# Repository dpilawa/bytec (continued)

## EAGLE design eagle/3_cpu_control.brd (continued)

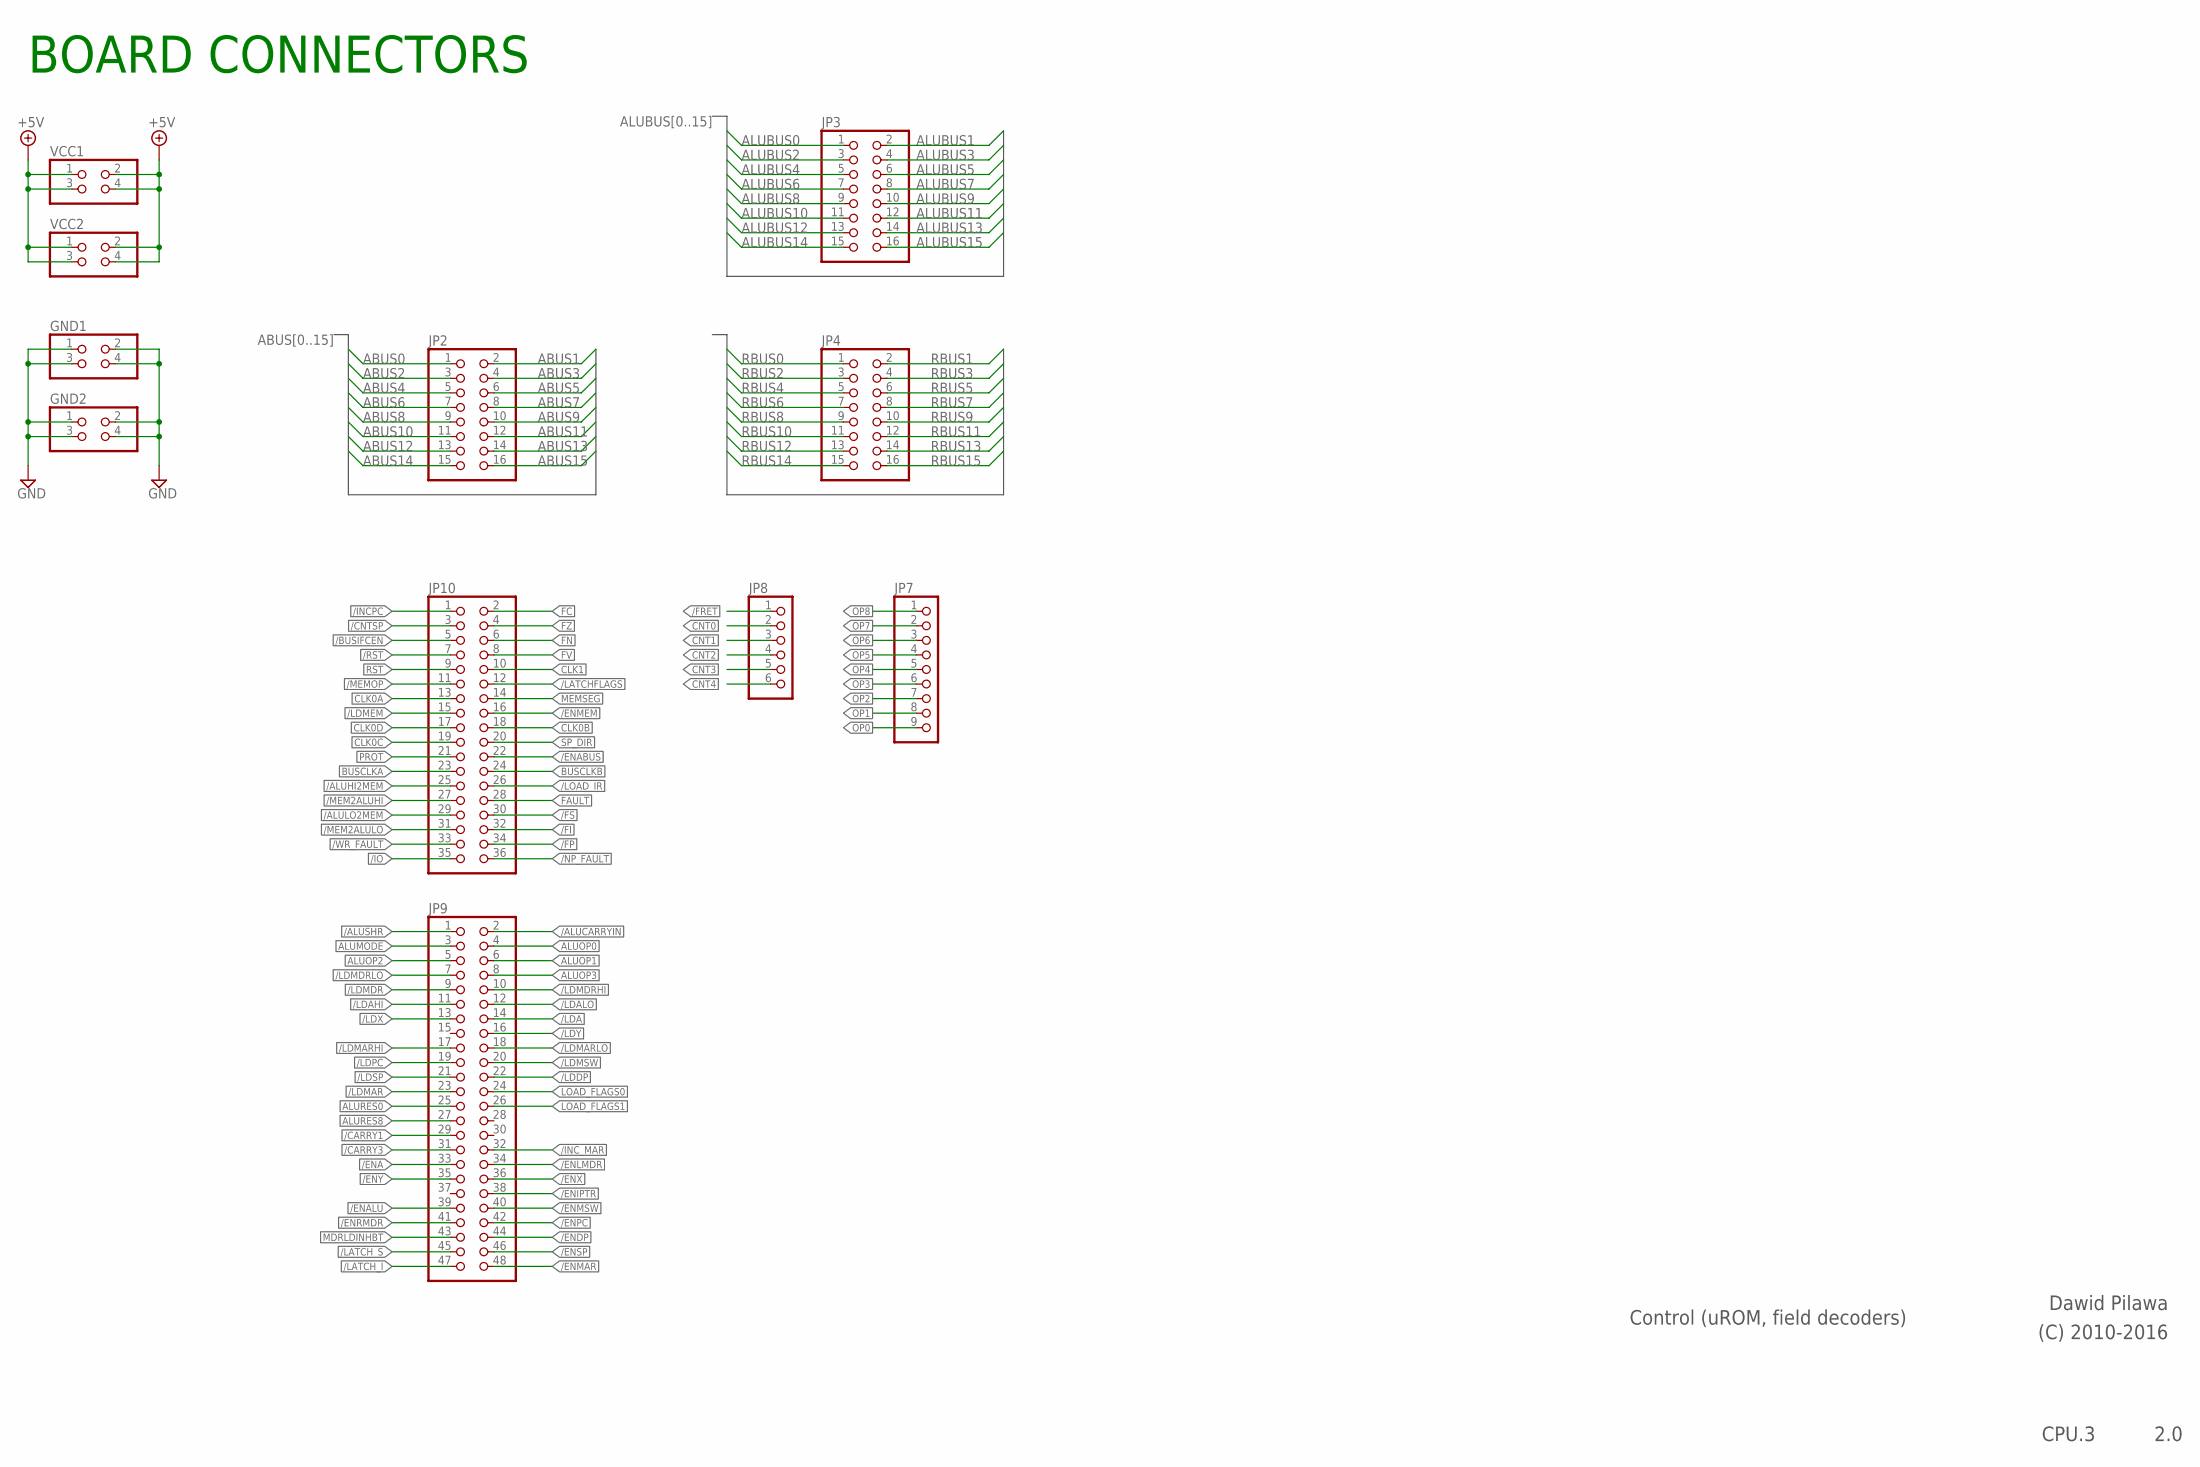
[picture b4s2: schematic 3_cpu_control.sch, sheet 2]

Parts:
GND1, GND2: PINHD-2X2; 2X02
JP2, JP3, JP4: PINHD-2X8; 2X08
JP7: PINHD-1X9; 1X09
JP8: PINHD-1X6; 1X06
JP9: PINHD-2X24; 2X24
JP10: PINHD-2X18; 2X18
VCC1, VCC2: PINHD-2X2; 2X02

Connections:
+5V: VCC1.1, VCC1.2, VCC1.3, VCC1.4, VCC2.1, VCC2.2, VCC2.3, VCC2.4; also elsewhere on the board
/ALUCARRYIN: JP9.2; also elsewhere on the board
/ALUHI2MEM: JP10.25; also elsewhere on the board
/ALULO2MEM: JP10.29; also elsewhere on the board
/ALUSHR: JP9.1; also elsewhere on the board
/BUSIFCEN: JP10.5; also elsewhere on the board
/CARRY1: JP9.29
/CARRY3: JP9.31
/CNTSP: JP10.3; also elsewhere on the board
/ENA: JP9.33; also elsewhere on the board
/ENABUS: JP10.22; also elsewhere on the board
/ENALU: JP9.39; also elsewhere on the board
/ENDP: JP9.44; also elsewhere on the board
/ENIPTR: JP9.38; also elsewhere on the board
/ENLMDR: JP9.34; also elsewhere on the board
/ENMAR: JP9.48; also elsewhere on the board
/ENMEM: JP10.16; also elsewhere on the board
/ENMSW: JP9.40; also elsewhere on the board
/ENPC: JP9.42; also elsewhere on the board
/ENRMDR: JP9.41; also elsewhere on the board
/ENSP: JP9.46; also elsewhere on the board
/ENX: JP9.36; also elsewhere on the board
/ENY: JP9.35; also elsewhere on the board
/FI: JP10.32
/FP: JP10.34
/FRET: JP8.1; also elsewhere on the board
/FS: JP10.30
/INCPC: JP10.1; also elsewhere on the board
/INC_MAR: JP9.32; also elsewhere on the board
/IO: JP10.35
/LATCHFLAGS: JP10.12; also elsewhere on the board
/LATCH_I: JP9.47; also elsewhere on the board
/LATCH_S: JP9.45; also elsewhere on the board
/LDA: JP9.14; also elsewhere on the board
/LDAHI: JP9.11; also elsewhere on the board
/LDALO: JP9.12; also elsewhere on the board
/LDDP: JP9.22; also elsewhere on the board
/LDMAR: JP9.23; also elsewhere on the board
/LDMARHI: JP9.17; also elsewhere on the board
/LDMARLO: JP9.18; also elsewhere on the board
/LDMDR: JP9.9; also elsewhere on the board
/LDMDRHI: JP9.10; also elsewhere on the board
/LDMDRLO: JP9.7; also elsewhere on the board
/LDMEM: JP10.15; also elsewhere on the board
/LDMSW: JP9.20; also elsewhere on the board
/LDPC: JP9.19; also elsewhere on the board
/LDSP: JP9.21; also elsewhere on the board
/LDX: JP9.13; also elsewhere on the board
/LDY: JP9.16; also elsewhere on the board
/LOAD_IR: JP10.26; also elsewhere on the board
/MEM2ALUHI: JP10.27; also elsewhere on the board
/MEM2ALULO: JP10.31; also elsewhere on the board
/MEMOP: JP10.11; also elsewhere on the board
/NP_FAULT: JP10.36
/RST: JP10.7
/WR_FAULT: JP10.33
ABUS0: JP2.1
ABUS1: JP2.2
ABUS2: JP2.3
ABUS3: JP2.4
ABUS4: JP2.5
ABUS5: JP2.6
ABUS6: JP2.7
ABUS7: JP2.8
ABUS8: JP2.9
ABUS9: JP2.10
ABUS10: JP2.11
ABUS11: JP2.12
ABUS12: JP2.13
ABUS13: JP2.14
ABUS14: JP2.15
ABUS15: JP2.16
ALUBUS0: JP3.1
ALUBUS1: JP3.2
ALUBUS2: JP3.3
ALUBUS3: JP3.4
ALUBUS4: JP3.5
ALUBUS5: JP3.6
ALUBUS6: JP3.7
ALUBUS7: JP3.8
ALUBUS8: JP3.9
ALUBUS9: JP3.10
ALUBUS10: JP3.11
ALUBUS11: JP3.12
ALUBUS12: JP3.13
ALUBUS13: JP3.14
ALUBUS14: JP3.15
ALUBUS15: JP3.16
ALUMODE: JP9.3; also elsewhere on the board
ALUOP0: JP9.4; also elsewhere on the board
ALUOP1: JP9.6; also elsewhere on the board
ALUOP2: JP9.5; also elsewhere on the board
ALUOP3: JP9.8; also elsewhere on the board
ALURES0: JP9.25
ALURES8: JP9.27
BUSCLKA: JP10.23; also elsewhere on the board
BUSCLKB: JP10.24
CLK0A: JP10.13
CLK0B: JP10.18
CLK0C: JP10.19
CLK0D: JP10.17; also elsewhere on the board
CLK1: JP10.10
CNT0: JP8.2; also elsewhere on the board
CNT1: JP8.3; also elsewhere on the board
CNT2: JP8.4; also elsewhere on the board
CNT3: JP8.5; also elsewhere on the board
CNT4: JP8.6; also elsewhere on the board
FAULT: JP10.28; also elsewhere on the board
FC: JP10.2; also elsewhere on the board
FN: JP10.6; also elsewhere on the board
FV: JP10.8; also elsewhere on the board
FZ: JP10.4; also elsewhere on the board
GND: GND1.1, GND1.2, GND1.3, GND1.4, GND2.1, GND2.2, GND2.3, GND2.4; also elsewhere on the board
LOAD_FLAGS0: JP9.24; also elsewhere on the board
LOAD_FLAGS1: JP9.26; also elsewhere on the board
MDRLDINHBT: JP9.43; also elsewhere on the board
MEMSEG: JP10.14; also elsewhere on the board
OP0: JP7.9; also elsewhere on the board
OP1: JP7.8; also elsewhere on the board
OP2: JP7.7; also elsewhere on the board
OP3: JP7.6; also elsewhere on the board
OP4: JP7.5; also elsewhere on the board
OP5: JP7.4; also elsewhere on the board
OP6: JP7.3; also elsewhere on the board
OP7: JP7.2; also elsewhere on the board
OP8: JP7.1; also elsewhere on the board
PROT: JP10.21; also elsewhere on the board
RBUS0: JP4.1
RBUS1: JP4.2
RBUS2: JP4.3
RBUS3: JP4.4
RBUS4: JP4.5
RBUS5: JP4.6
RBUS6: JP4.7
RBUS7: JP4.8
RBUS8: JP4.9
RBUS9: JP4.10
RBUS10: JP4.11
RBUS11: JP4.12
RBUS12: JP4.13
RBUS13: JP4.14
RBUS14: JP4.15
RBUS15: JP4.16
RST: JP10.9
SP_DIR: JP10.20; also elsewhere on the board

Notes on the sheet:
Control (uROM, field decoders)
2.0
Dawid Pilawa
(C) 2010-2016
CPU.3
BOARD CONNECTORS

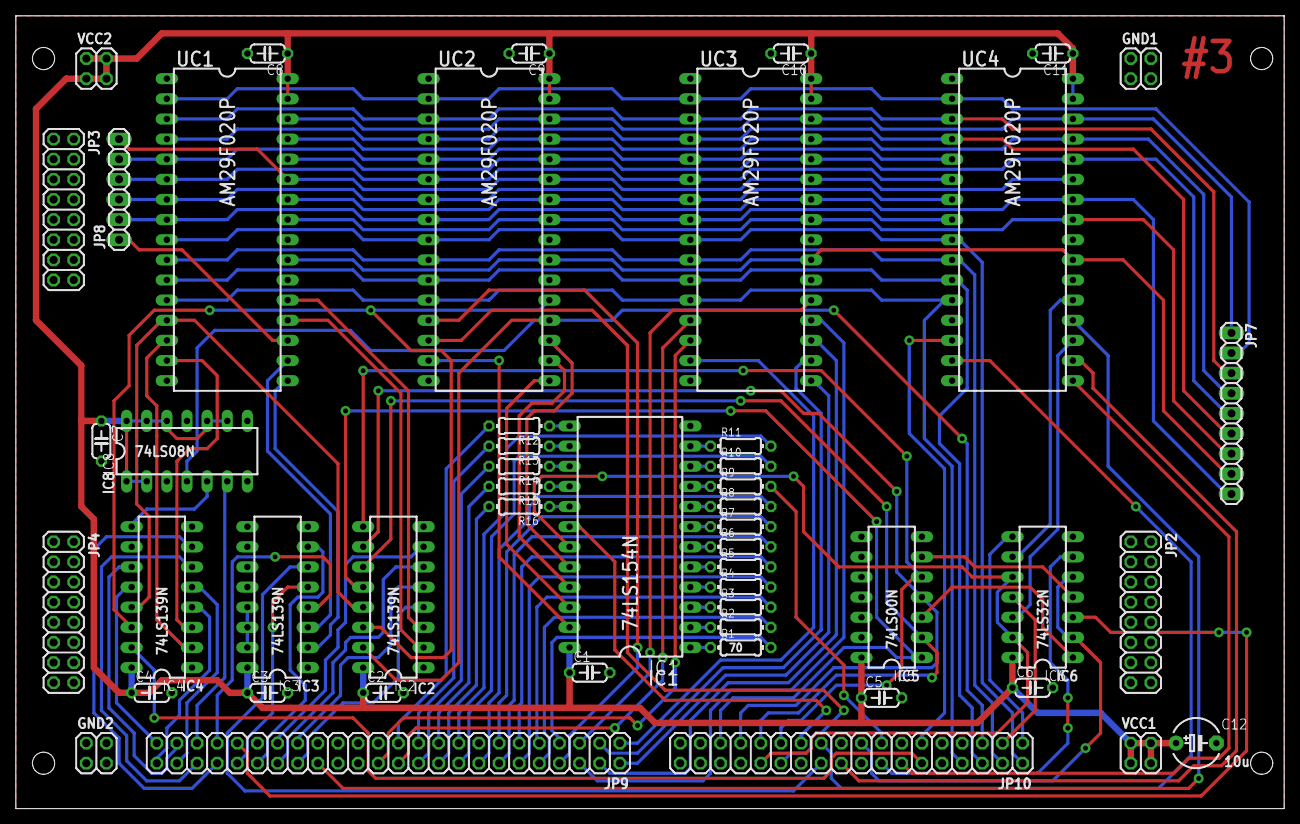
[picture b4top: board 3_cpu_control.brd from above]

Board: 2 copper layers, 160.0 x 100.0 mm, 50 parts (0 on the bottom side), 113 nets.

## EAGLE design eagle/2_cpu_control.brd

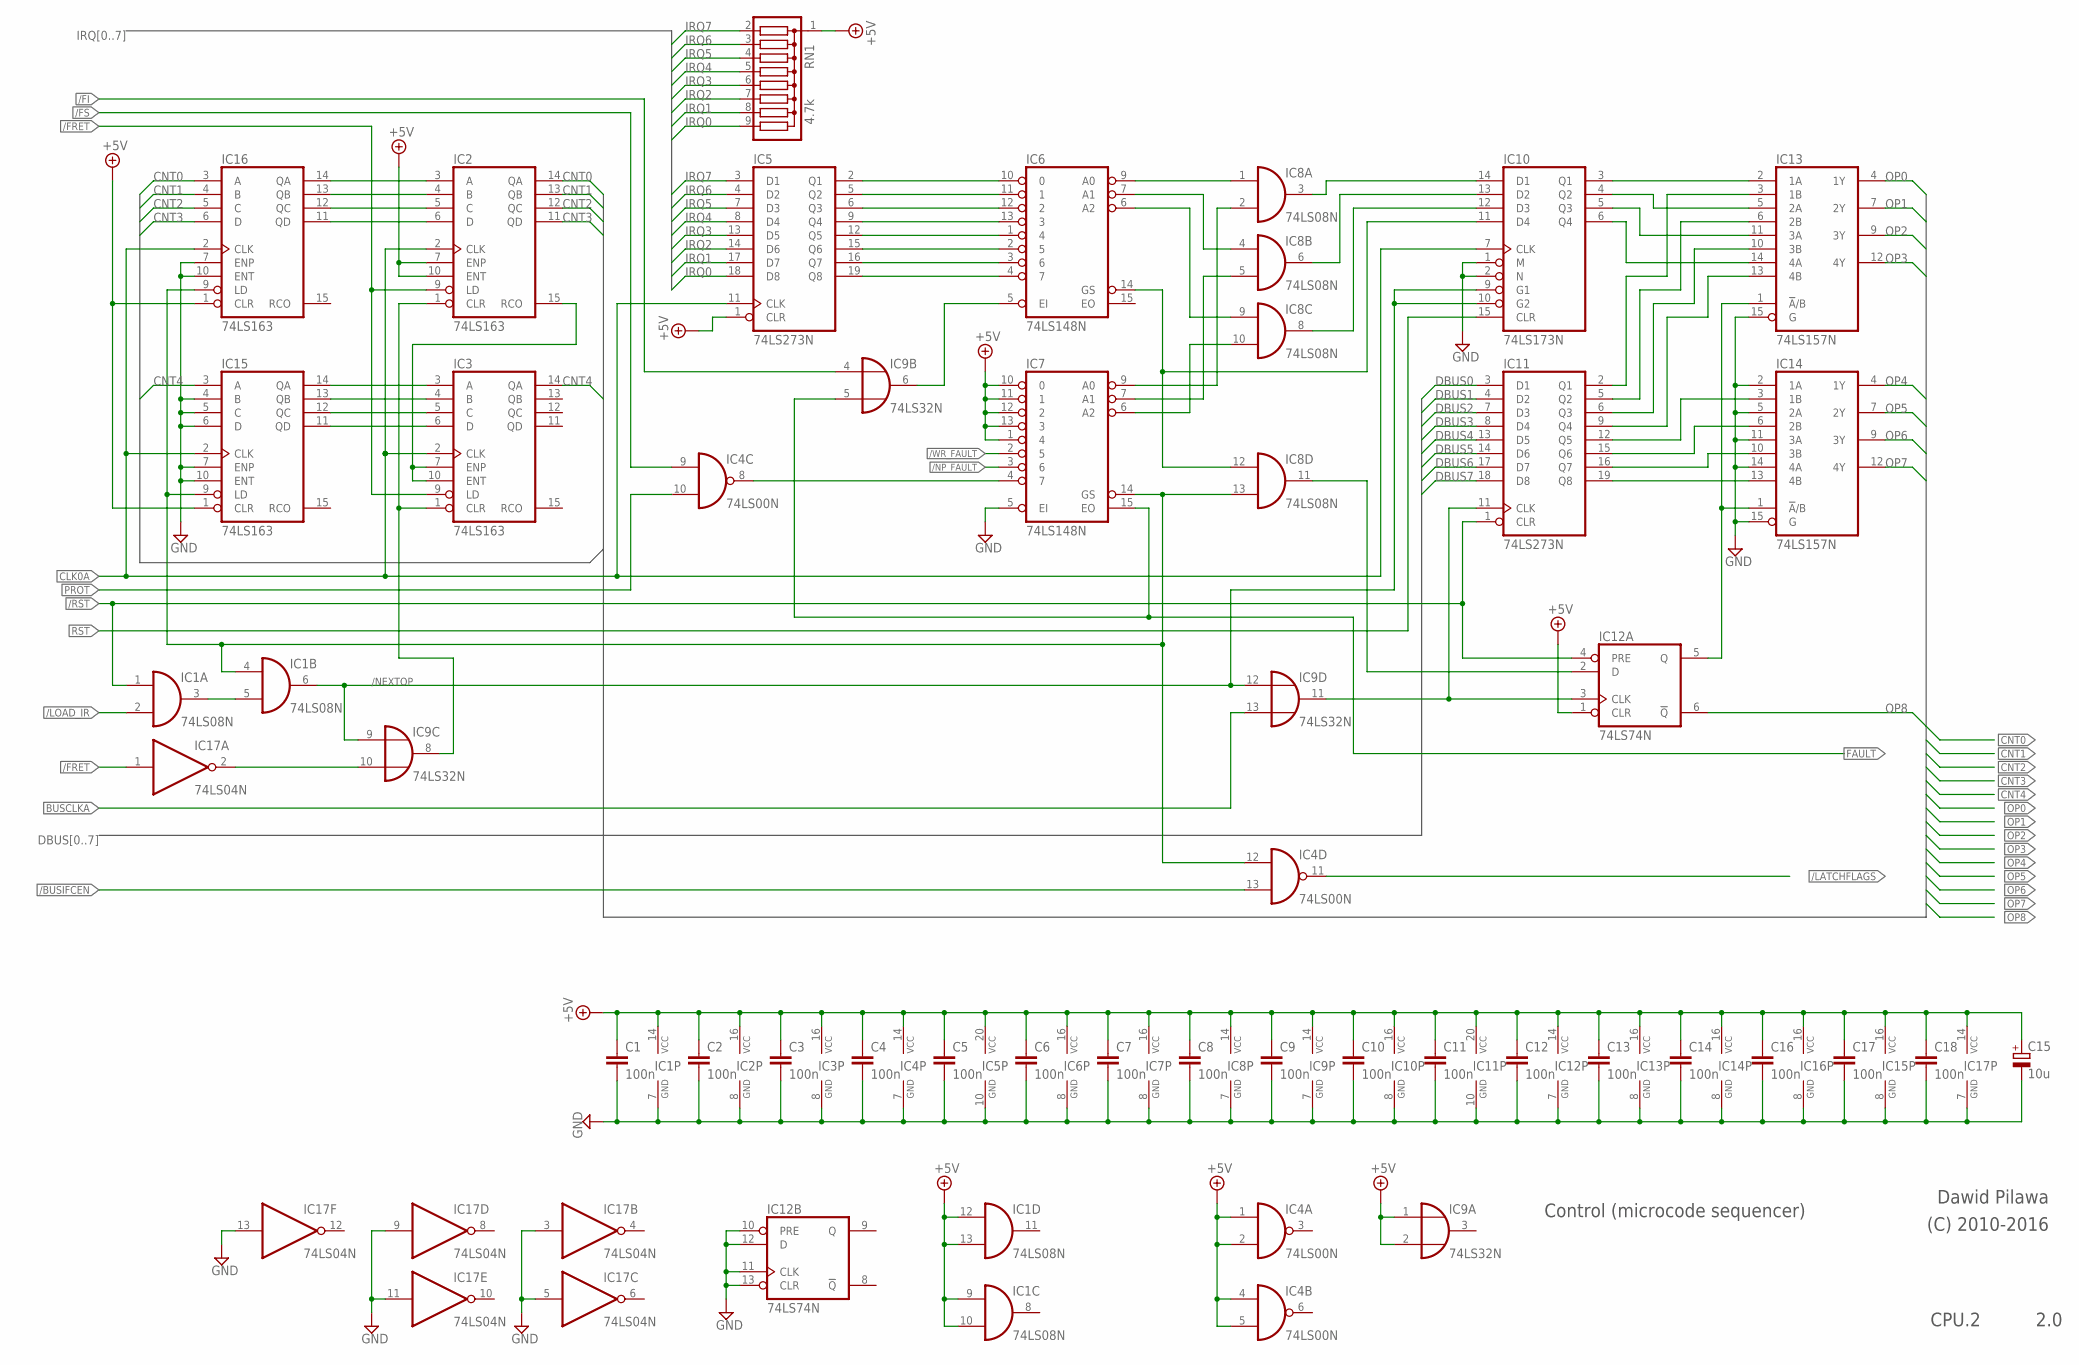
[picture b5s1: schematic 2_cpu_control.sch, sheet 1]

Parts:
C1, C2, C3, C4, C5, C6, C7, C8, C9, C10, C11, C12, C13, C14, C16, C17, C18: 100n; C050-024X044
C15: 10u; E5-6
IC1, IC8: 74LS08N; DIL14
IC2, IC3, IC15, IC16: 74LS163; DIL16
IC4: 74LS00N; DIL14
IC5, IC11: 74LS273N; DIL20
IC6, IC7: 74LS148N; DIL16
IC9: 74LS32N; DIL14
IC10: 74LS173N; DIL16
IC12: 74LS74N; DIL14
IC13, IC14: 74LS157N; DIL16
IC17: 74LS04N; DIL14
RN1: 4.7k; SIL9

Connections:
+5V: C1.1, C2.1, C3.1, C4.1, C5.1, C6.1, C7.1, C8.1, C9.1, C10.1, C11.1, C12.1, C13.1, C14.1, C15.+, C16.1, C17.1, C18.1, IC1.9 (I0), IC1.10 (I1), IC1.12 (I0), IC1.13 (I1), IC1.14 (VCC), IC2.7 (ENP), IC2.10 (ENT), IC2.16 (VCC), IC3.16 (VCC), IC4.1 (I0), IC4.2 (I1), IC4.4 (I0), IC4.5 (I1), IC4.14 (VCC), IC5.1 (CLR), IC5.20 (VCC), IC6.16 (VCC), IC7.1 (4), IC7.10 (0), IC7.11 (1), IC7.12 (2), IC7.13 (3), IC7.16 (VCC), IC8.14 (VCC), IC9.1 (I0), IC9.2 (I1), IC9.14 (VCC), IC10.16 (VCC), IC11.20 (VCC), IC12.1 (CLR), IC12.14 (VCC), IC13.16 (VCC), IC14.16 (VCC), IC15.1 (CLR), IC15.16 (VCC), IC16.1 (CLR), IC16.16 (VCC), IC17.14 (VCC), RN1.1; also elsewhere on the board
/BUSIFCEN: IC4.13 (I1); also elsewhere on the board
/FAULT_PF: IC4.8 (O), IC7.4 (7)
/FI: IC9.4 (I0); also elsewhere on the board
/FRET: IC2.9 (LD), IC3.9 (LD), IC17.1 (I); also elsewhere on the board
/FS: IC4.9 (I0); also elsewhere on the board
/LATCHFLAGS: IC4.11 (O); also elsewhere on the board
/LOAD_IR: IC1.2 (I1); also elsewhere on the board
/NEXTOP: IC1.6 (O), IC9.9 (I0), IC9.12 (I0), IC10.9 (G1), IC10.10 (G2)
/NP_FAULT: IC7.3 (6); also elsewhere on the board
/RST: IC1.1 (I0), IC11.1 (CLR), IC12.4 (PRE); also elsewhere on the board
/WR_FAULT: IC7.2 (5); also elsewhere on the board
BUSCLKA: IC9.13 (I1); also elsewhere on the board
CLK0A: IC2.2 (CLK), IC3.2 (CLK), IC5.11 (CLK), IC10.7 (CLK), IC15.2 (CLK), IC16.2 (CLK); also elsewhere on the board
CNT0: IC2.14 (QA), IC16.3 (A); also elsewhere on the board
CNT1: IC2.13 (QB), IC16.4 (B); also elsewhere on the board
CNT2: IC2.12 (QC), IC16.5 (C); also elsewhere on the board
CNT3: IC2.11 (QD), IC16.6 (D); also elsewhere on the board
CNT4: IC3.14 (QA), IC15.3 (A); also elsewhere on the board
DBUS0: IC11.3 (D1); also elsewhere on the board
DBUS1: IC11.4 (D2); also elsewhere on the board
DBUS2: IC11.7 (D3); also elsewhere on the board
DBUS3: IC11.8 (D4); also elsewhere on the board
DBUS4: IC11.13 (D5); also elsewhere on the board
DBUS5: IC11.14 (D6); also elsewhere on the board
DBUS6: IC11.17 (D7); also elsewhere on the board
DBUS7: IC11.18 (D8); also elsewhere on the board
FAULT: IC7.15 (EO), IC9.5 (I1); also elsewhere on the board
GND: C1.2, C2.2, C3.2, C4.2, C5.2, C6.2, C7.2, C8.2, C9.2, C10.2, C11.2, C12.2, C13.2, C14.2, C15.-, C16.2, C17.2, C18.2, IC1.7 (GND), IC2.8 (GND), IC3.8 (GND), IC4.7 (GND), IC5.10 (GND), IC6.8 (GND), IC7.5 (EI), IC7.8 (GND), IC8.7 (GND), IC9.7 (GND), IC10.1 (M), IC10.2 (N), IC10.8 (GND), IC11.10 (GND), IC12.7 (GND), IC12.10 (PRE), IC12.11 (CLK), IC12.12 (D), IC12.13 (CLR), IC13.8 (GND), IC13.15 (G), IC14.2 (1A), IC14.5 (2A), IC14.8 (GND), IC14.11 (3A), IC14.14 (4A), IC14.15 (G), IC15.4 (B), IC15.5 (C), IC15.6 (D), IC15.7 (ENP), IC15.8 (GND), IC15.10 (ENT), IC16.7 (ENP), IC16.8 (GND), IC16.10 (ENT), IC17.3 (I), IC17.5 (I), IC17.7 (GND), IC17.9 (I), IC17.11 (I), IC17.13 (I); also elsewhere on the board
IRQ0: IC5.18 (D8), RN1.9; also elsewhere on the board
IRQ1: IC5.17 (D7), RN1.8; also elsewhere on the board
IRQ2: IC5.14 (D6), RN1.7; also elsewhere on the board
IRQ3: IC5.13 (D5), RN1.6; also elsewhere on the board
IRQ4: IC5.8 (D4), RN1.5; also elsewhere on the board
IRQ5: IC5.7 (D3), RN1.4; also elsewhere on the board
IRQ6: IC5.4 (D2), RN1.3; also elsewhere on the board
IRQ7: IC5.3 (D1), RN1.2; also elsewhere on the board
unnamed: IC6.9 (A0), IC8.1 (I0)
unnamed: IC2.15 (RCO), IC3.7 (ENP), IC3.10 (ENT)
unnamed: IC7.9 (A0), IC8.2 (I1)
unnamed: IC6.7 (A1), IC8.4 (I0)
unnamed: IC7.7 (A1), IC8.5 (I1)
unnamed: IC7.6 (A2), IC8.10 (I1)
unnamed: IC6.6 (A2), IC8.9 (I0)
unnamed: IC1.3 (O), IC1.5 (I1)
unnamed: IC6.14 (GS), IC8.12 (I0), IC10.11 (D4)
unnamed: IC1.4 (I0), IC4.12 (I0), IC7.14 (GS), IC8.13 (I1), IC15.9 (LD), IC16.9 (LD)
unnamed: IC8.3 (O), IC10.14 (D1)
unnamed: IC8.6 (O), IC10.13 (D2)
unnamed: IC8.8 (O), IC10.12 (D3)
unnamed: IC8.11 (O), IC12.2 (D)
unnamed: IC9.10 (I1), IC17.2 (O)
unnamed: IC11.5 (Q2), IC13.6 (2B)
unnamed: IC9.11 (O), IC11.11 (CLK), IC12.3 (CLK)
unnamed: IC10.3 (Q1), IC13.2 (1A)
unnamed: IC10.4 (Q2), IC13.5 (2A)
unnamed: IC10.5 (Q3), IC13.11 (3A)
unnamed: IC10.6 (Q4), IC13.14 (4A)
unnamed: IC11.19 (Q8), IC14.13 (4B)
unnamed: IC11.16 (Q7), IC14.10 (3B)
unnamed: IC11.15 (Q6), IC14.6 (2B)
unnamed: IC11.12 (Q5), IC14.3 (1B)
unnamed: IC11.2 (Q1), IC13.3 (1B)
unnamed: IC6.5 (EI), IC9.6 (O)
unnamed: IC11.6 (Q3), IC13.10 (3B)
unnamed: IC3.5 (C), IC15.12 (QC)
unnamed: IC11.9 (Q4), IC13.13 (4B)
unnamed: IC2.5 (C), IC16.12 (QC)
unnamed: IC2.3 (A), IC16.14 (QA)
unnamed: IC2.4 (B), IC16.13 (QB)
unnamed: IC2.6 (D), IC16.11 (QD)
unnamed: IC3.3 (A), IC15.14 (QA)
unnamed: IC3.4 (B), IC15.13 (QB)
unnamed: IC3.6 (D), IC15.11 (QD)
unnamed: IC2.1 (CLR), IC3.1 (CLR), IC9.8 (O)
unnamed: IC12.5 (Q), IC13.1 (!A!/B), IC14.1 (!A!/B)
unnamed: IC5.19 (Q8), IC6.4 (7)
unnamed: IC5.16 (Q7), IC6.3 (6)
unnamed: IC5.15 (Q6), IC6.2 (5)
unnamed: IC5.12 (Q5), IC6.1 (4)
unnamed: IC5.9 (Q4), IC6.13 (3)
unnamed: IC5.6 (Q3), IC6.12 (2)
unnamed: IC5.5 (Q2), IC6.11 (1)
unnamed: IC5.2 (Q1), IC6.10 (0)
OP0: IC13.4 (1Y); also elsewhere on the board
OP1: IC13.7 (2Y); also elsewhere on the board
OP2: IC13.9 (3Y); also elsewhere on the board
OP3: IC13.12 (4Y); also elsewhere on the board
OP4: IC14.4 (1Y); also elsewhere on the board
OP5: IC14.7 (2Y); also elsewhere on the board
OP6: IC14.9 (3Y); also elsewhere on the board
OP7: IC14.12 (4Y); also elsewhere on the board
OP8: IC12.6 (!Q); also elsewhere on the board
PROT: IC4.10 (I1); also elsewhere on the board
RST: IC10.15 (CLR); also elsewhere on the board

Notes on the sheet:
Control (microcode sequencer)
2.0
Dawid Pilawa
(C) 2010-2016
CPU.2

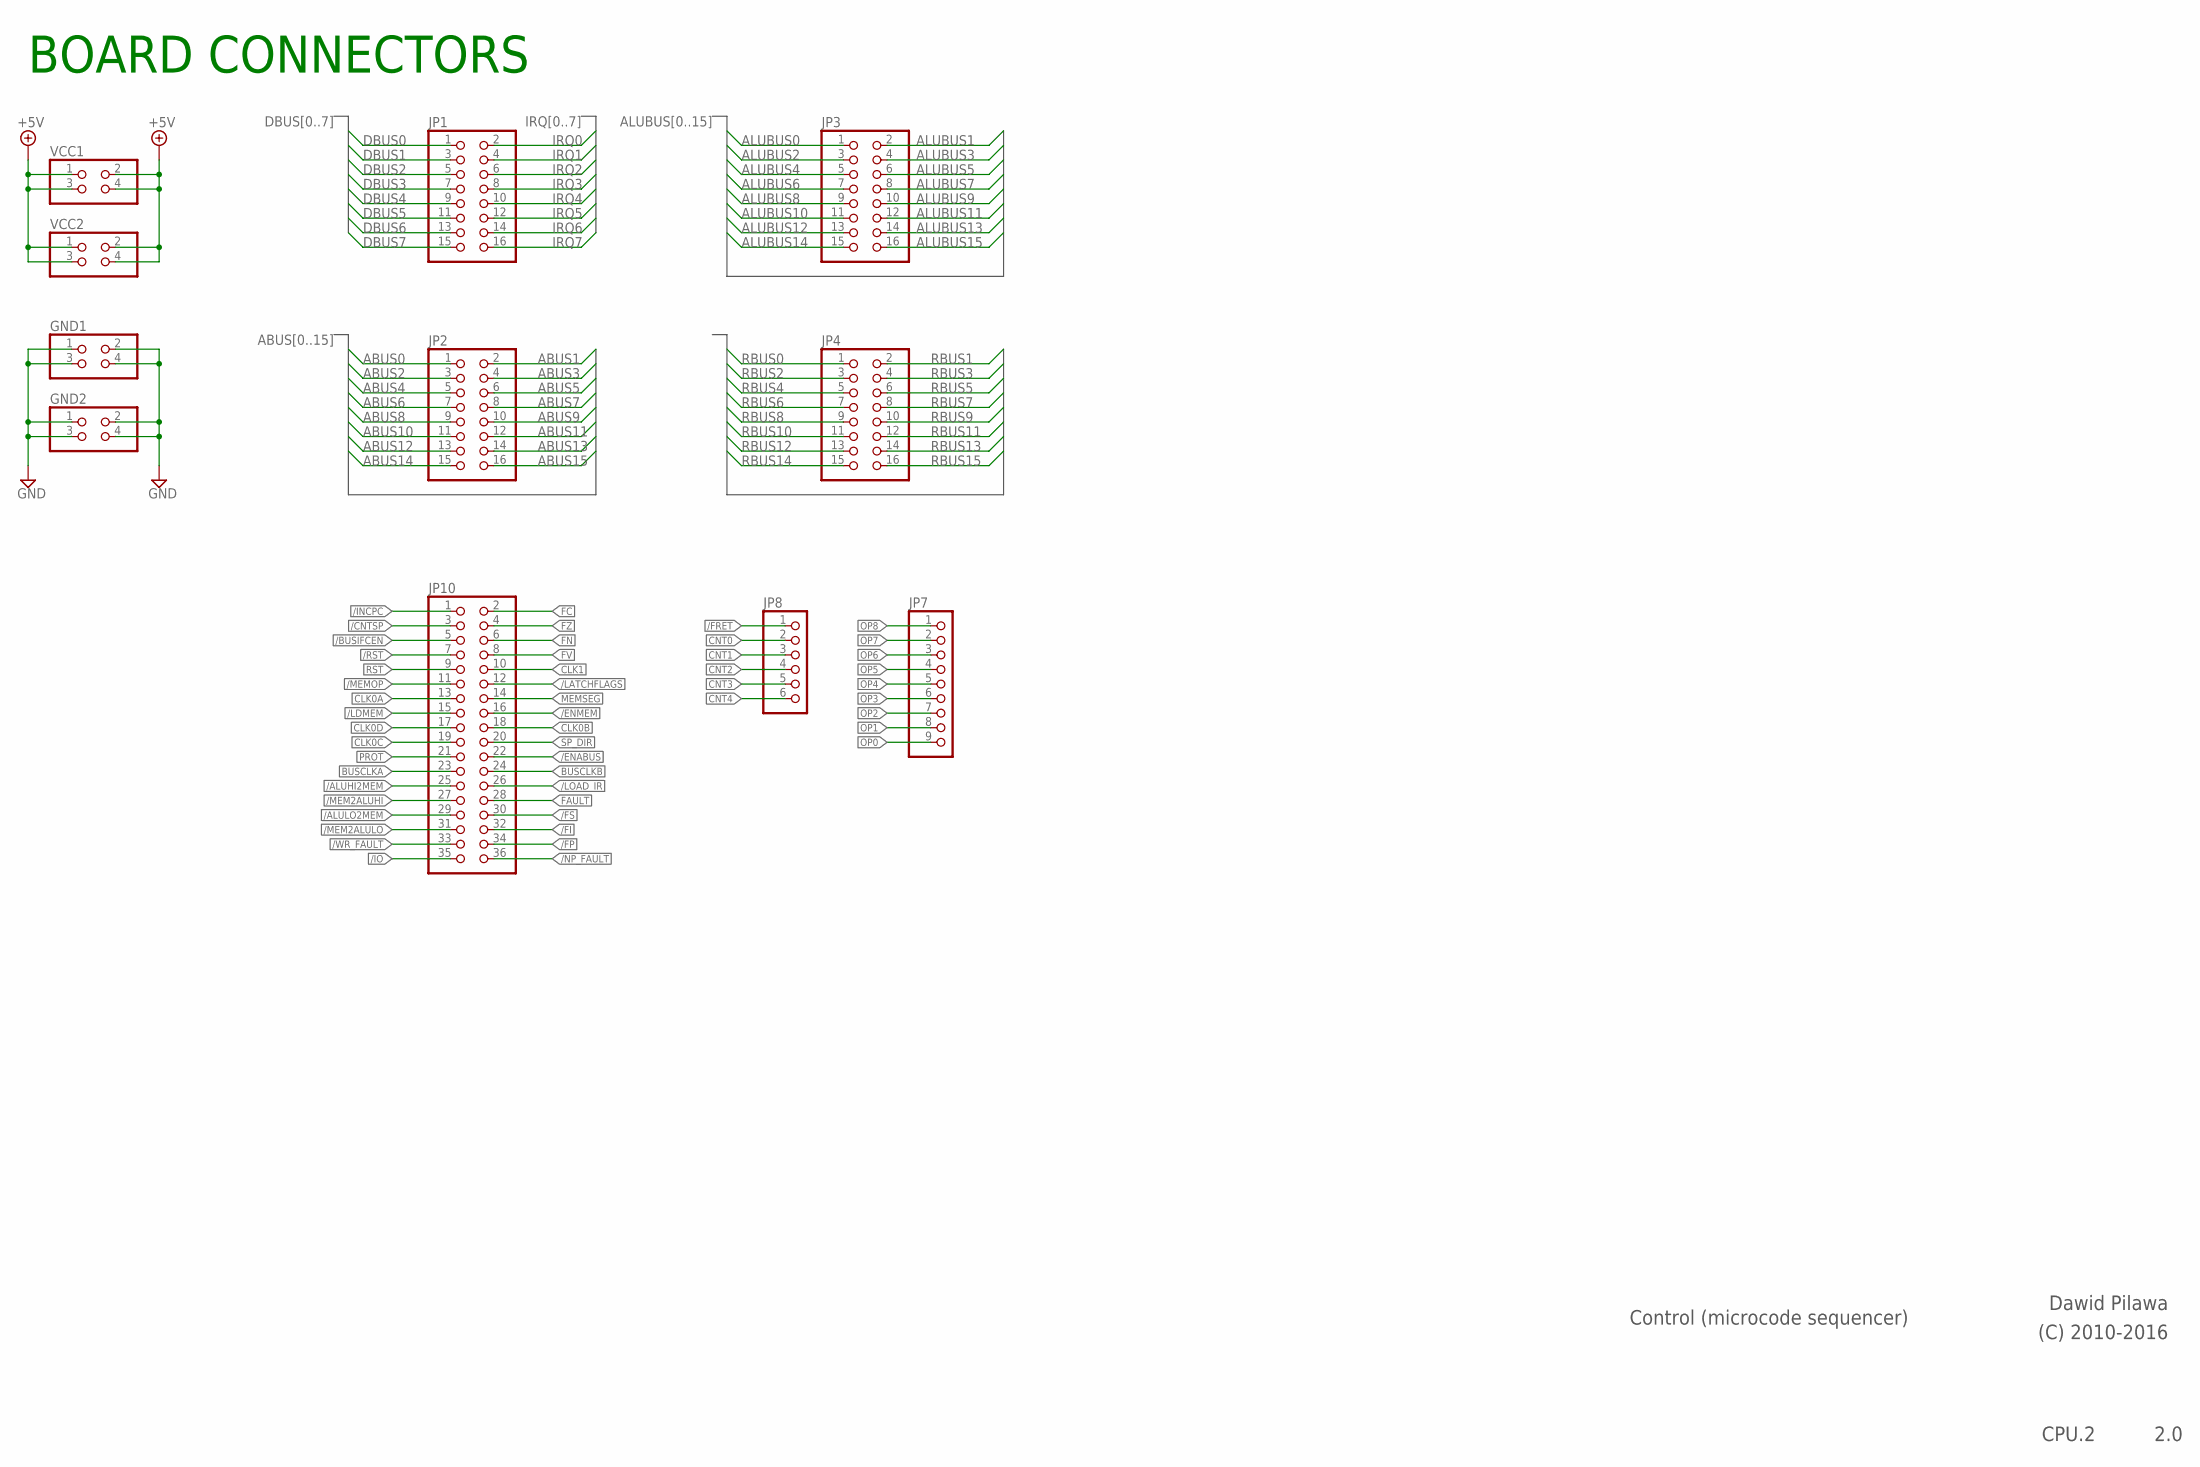
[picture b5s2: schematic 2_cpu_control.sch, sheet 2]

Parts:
GND1, GND2: PINHD-2X2; 2X02
JP1, JP2, JP3, JP4: PINHD-2X8; 2X08
JP7: PINHD-1X9; 1X09
JP8: PINHD-1X6; 1X06
JP10: PINHD-2X18; 2X18
VCC1, VCC2: PINHD-2X2; 2X02

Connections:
+5V: VCC1.1, VCC1.2, VCC1.3, VCC1.4, VCC2.1, VCC2.2, VCC2.3, VCC2.4; also elsewhere on the board
/ALUHI2MEM: JP10.25
/ALULO2MEM: JP10.29
/BUSIFCEN: JP10.5; also elsewhere on the board
/CNTSP: JP10.3
/ENABUS: JP10.22
/ENMEM: JP10.16
/FI: JP10.32; also elsewhere on the board
/FP: JP10.34
/FRET: JP8.1; also elsewhere on the board
/FS: JP10.30; also elsewhere on the board
/INCPC: JP10.1
/IO: JP10.35
/LATCHFLAGS: JP10.12; also elsewhere on the board
/LDMEM: JP10.15
/LOAD_IR: JP10.26; also elsewhere on the board
/MEM2ALUHI: JP10.27
/MEM2ALULO: JP10.31
/MEMOP: JP10.11
/NP_FAULT: JP10.36; also elsewhere on the board
/RST: JP10.7; also elsewhere on the board
/WR_FAULT: JP10.33; also elsewhere on the board
ABUS0: JP2.1
ABUS1: JP2.2
ABUS2: JP2.3
ABUS3: JP2.4
ABUS4: JP2.5
ABUS5: JP2.6
ABUS6: JP2.7
ABUS7: JP2.8
ABUS8: JP2.9
ABUS9: JP2.10
ABUS10: JP2.11
ABUS11: JP2.12
ABUS12: JP2.13
ABUS13: JP2.14
ABUS14: JP2.15
ABUS15: JP2.16
ALUBUS0: JP3.1
ALUBUS1: JP3.2
ALUBUS2: JP3.3
ALUBUS3: JP3.4
ALUBUS4: JP3.5
ALUBUS5: JP3.6
ALUBUS6: JP3.7
ALUBUS7: JP3.8
ALUBUS8: JP3.9
ALUBUS9: JP3.10
ALUBUS10: JP3.11
ALUBUS11: JP3.12
ALUBUS12: JP3.13
ALUBUS13: JP3.14
ALUBUS14: JP3.15
ALUBUS15: JP3.16
BUSCLKA: JP10.23; also elsewhere on the board
BUSCLKB: JP10.24
CLK0A: JP10.13; also elsewhere on the board
CLK0B: JP10.18
CLK0C: JP10.19
CLK0D: JP10.17
CLK1: JP10.10
CNT0: JP8.2; also elsewhere on the board
CNT1: JP8.3; also elsewhere on the board
CNT2: JP8.4; also elsewhere on the board
CNT3: JP8.5; also elsewhere on the board
CNT4: JP8.6; also elsewhere on the board
DBUS0: JP1.1; also elsewhere on the board
DBUS1: JP1.3; also elsewhere on the board
DBUS2: JP1.5; also elsewhere on the board
DBUS3: JP1.7; also elsewhere on the board
DBUS4: JP1.9; also elsewhere on the board
DBUS5: JP1.11; also elsewhere on the board
DBUS6: JP1.13; also elsewhere on the board
DBUS7: JP1.15; also elsewhere on the board
FAULT: JP10.28; also elsewhere on the board
FC: JP10.2
FN: JP10.6
FV: JP10.8
FZ: JP10.4
GND: GND1.1, GND1.2, GND1.3, GND1.4, GND2.1, GND2.2, GND2.3, GND2.4; also elsewhere on the board
IRQ0: JP1.2; also elsewhere on the board
IRQ1: JP1.4; also elsewhere on the board
IRQ2: JP1.6; also elsewhere on the board
IRQ3: JP1.8; also elsewhere on the board
IRQ4: JP1.10; also elsewhere on the board
IRQ5: JP1.12; also elsewhere on the board
IRQ6: JP1.14; also elsewhere on the board
IRQ7: JP1.16; also elsewhere on the board
MEMSEG: JP10.14
OP0: JP7.9; also elsewhere on the board
OP1: JP7.8; also elsewhere on the board
OP2: JP7.7; also elsewhere on the board
OP3: JP7.6; also elsewhere on the board
OP4: JP7.5; also elsewhere on the board
OP5: JP7.4; also elsewhere on the board
OP6: JP7.3; also elsewhere on the board
OP7: JP7.2; also elsewhere on the board
OP8: JP7.1; also elsewhere on the board
PROT: JP10.21; also elsewhere on the board
RBUS0: JP4.1
RBUS1: JP4.2
RBUS2: JP4.3
RBUS3: JP4.4
RBUS4: JP4.5
RBUS5: JP4.6
RBUS6: JP4.7
RBUS7: JP4.8
RBUS8: JP4.9
RBUS9: JP4.10
RBUS10: JP4.11
RBUS11: JP4.12
RBUS12: JP4.13
RBUS13: JP4.14
RBUS14: JP4.15
RBUS15: JP4.16
RST: JP10.9; also elsewhere on the board
SP_DIR: JP10.20

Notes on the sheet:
Control (microcode sequencer)
2.0
Dawid Pilawa
(C) 2010-2016
CPU.2
BOARD CONNECTORS

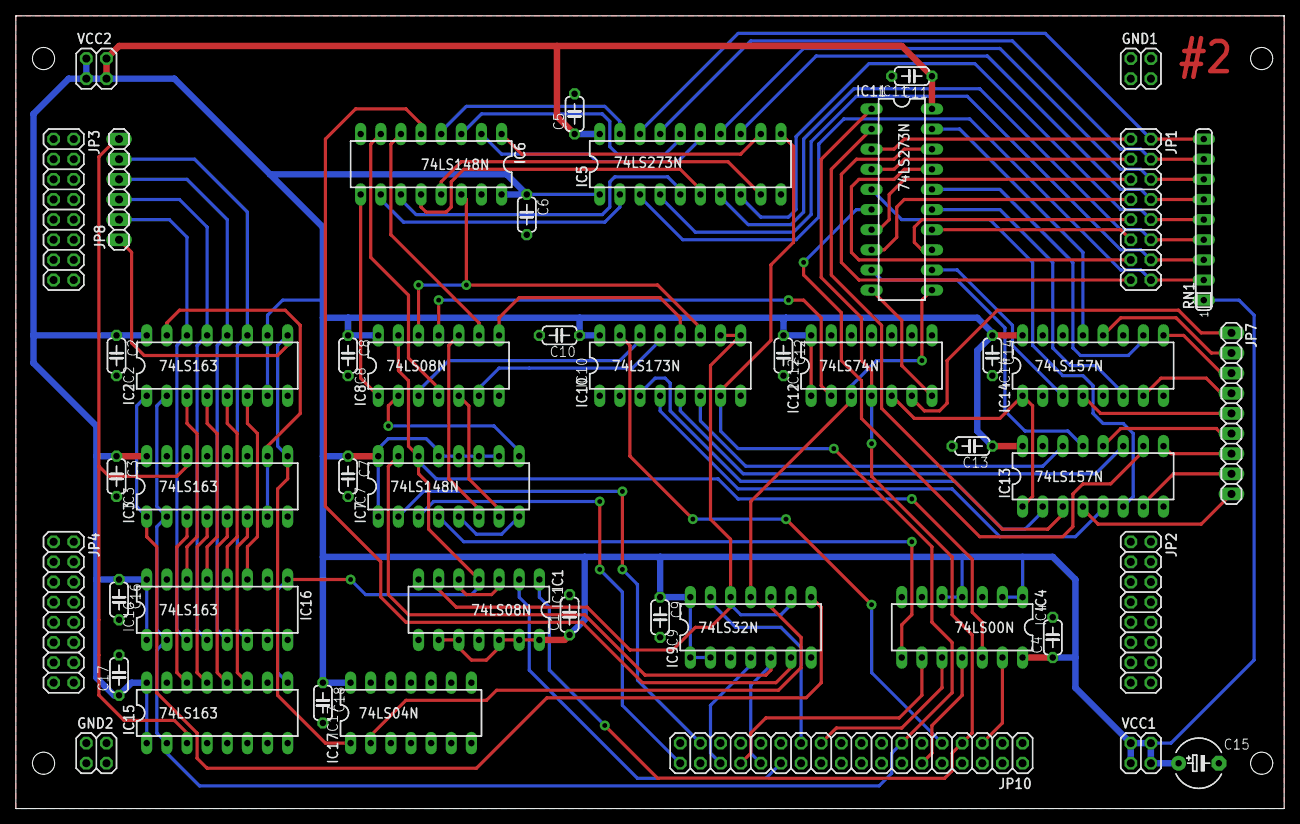
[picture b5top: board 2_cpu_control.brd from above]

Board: 2 copper layers, 160.0 x 100.0 mm, 47 parts (0 on the bottom side), 95 nets.
